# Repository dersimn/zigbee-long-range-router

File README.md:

# CC2530+CC2592 Long Range ZigBee Router
Mod of cod.m's [Zigbee Long Range Router](https://shop.codm.de/automation/zigbee/23/zigbee-cc2530-cc2592-long-range-router/repeater) based on EByte's [E18-MS1PA2-PCB](http://www.ebyte.com/en/product-view-news.aspx?id=988) sporting an CC2530 combined with an CC2592 PA/LNA for range extension.

The corresponding eagle library for the EByte modules, including 3D models, can be found here: https://github.com/codm/eagle-libraries

You can buy a ready built router, including external antenna, 3D printed case and power supply at our webshop: [CC2530-CC2592 Long Range ZigBee Router](https://shop.codm.de/automation/zigbee/23/zigbee-cc2530-cc2592-long-range-router/repeater)

# Firmware
Thanks to https://ptvo.info and his [configurable ZigBee Firmware](https://ptvo.info/zigbee-switch-configurable-firmware-v2-210/), we've built our own version of the firmware - based on Z-Stack 1.2 - to make use of the onboard LED.

See zigbee2mqtt's FAQ for more info on how to use ZigBee routers and expand your current ZigBee mesh: https://www.zigbee2mqtt.io/information/FAQ.html#i-read-that-zigbee2mqtt-has-a-limit-of-20-devices-is-this-true

## Upgrading
You can flash the module with a another/new firmware using an CC-Debugger from TI, which is also used for the common CC2531-USB-Sticks. The pin header on the top has the same layout.

# License
[CC-BY-SA-NC 3.0](https://creativecommons.org/licenses/by-nc-sa/3.0/de/)

Credits:
- cod.m GmbH, Patrik Mayer, 2020
- [Simon Christmann](https://github.com/dersimn), 2020

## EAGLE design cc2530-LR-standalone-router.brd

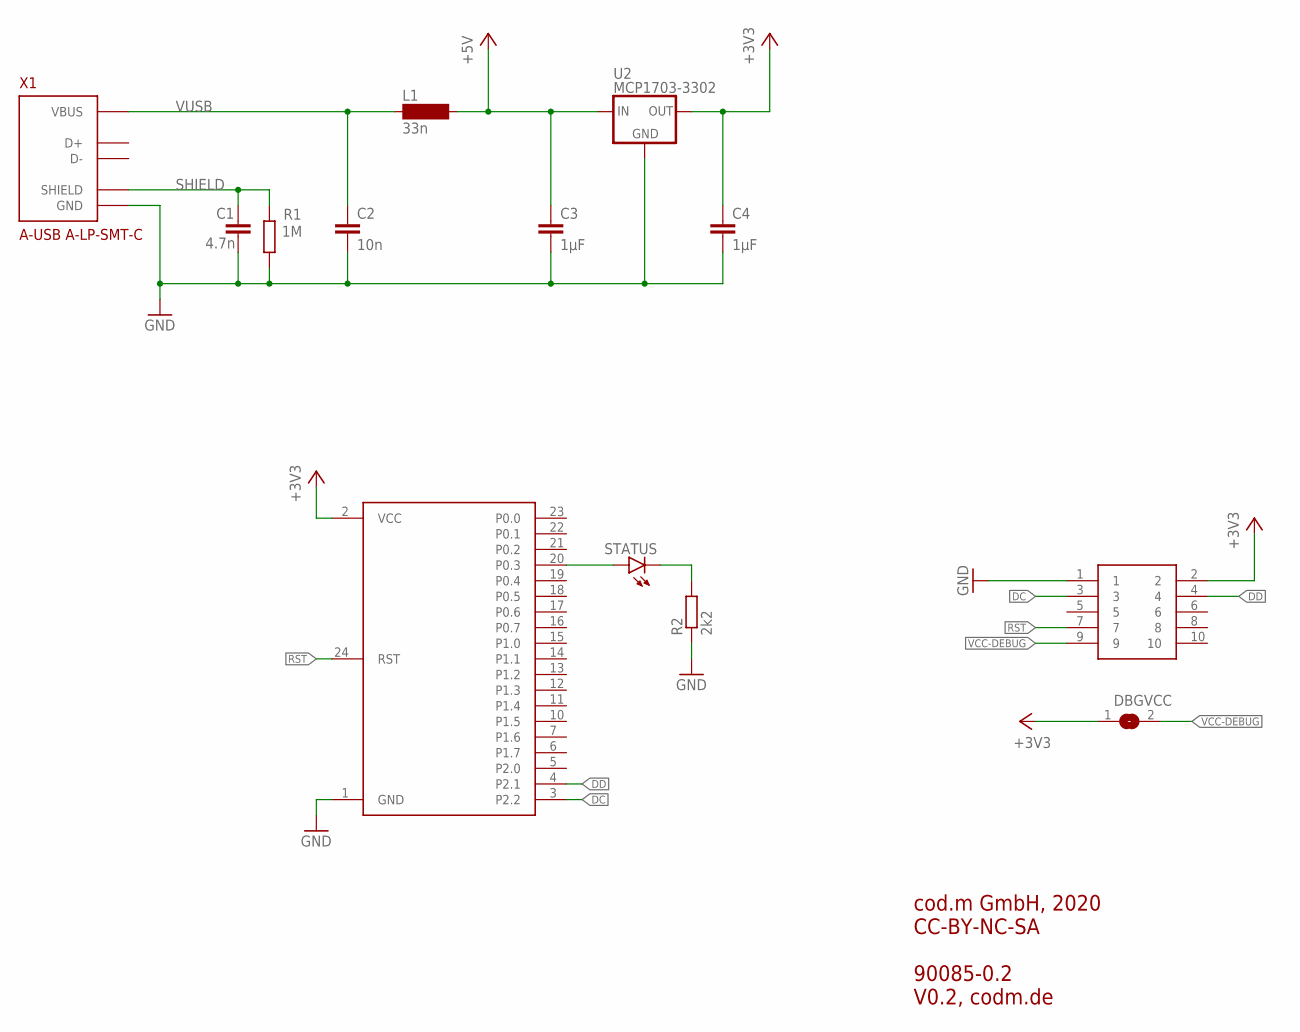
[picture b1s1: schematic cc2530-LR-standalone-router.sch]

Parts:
C1: 4.7n; C1206
C2: 10n; C1206
C3, C4: 1µF; C1206
DBGVCC: SJ
DEBUG: 20021121-00010C4LF; 2002112100010C4LF
L1: 33n; SM-1206
R1: 1M; R1206
R2: 2k2; R1206
STATUS: LEDCHIPLED_1206; CHIPLED_1206
U2: MCP1703-3302; SOT-22-3
U$5: E18-MS1PA2-PCB
X1: A-USB A-LP-SMT-C; A-USB_A-LP-SMT-C

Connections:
+3V3: C4.1, DBGVCC.1, DEBUG.2, U2.3 (OUT), U$5.2 (VCC)
+5V: C3.1, L1.2, U2.1 (IN)
DC: DEBUG.3, U$5.3 (P2.2)
DD: DEBUG.4, U$5.4 (P2.1)
GND: C1.2, C2.2, C3.2, C4.2, DEBUG.1, R1.2, R2.1, U2.2 (GND), U2.4 (GND), U$5.1 (GND), X1.4 (GND)
unnamed: R2.2, STATUS.C
unnamed: STATUS.A, U$5.20 (P0.3)
RST: DEBUG.7, U$5.24 (RST)
SHIELD: C1.1, R1.1, X1.S1 (SHIELD), X1.S2 (SHIELD)
VCC-DEBUG: DBGVCC.2, DEBUG.9
VUSB: C2.1, L1.1, X1.1 (VBUS)

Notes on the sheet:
cod.m GmbH, 2020 CC-BY-NC-SA 90085-0.2 V0.2, codm.de

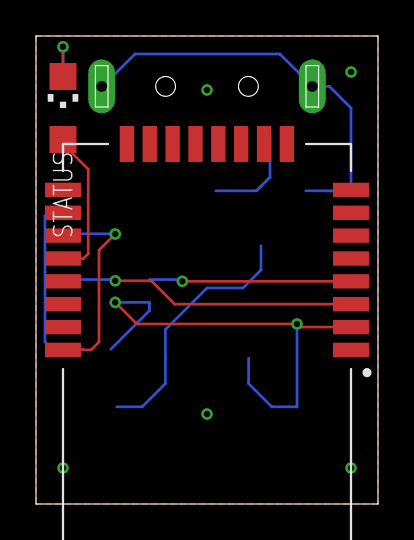
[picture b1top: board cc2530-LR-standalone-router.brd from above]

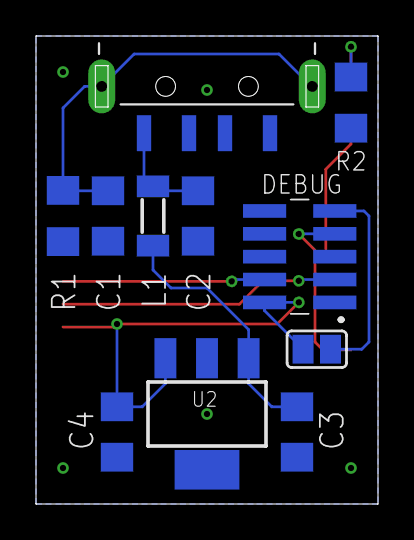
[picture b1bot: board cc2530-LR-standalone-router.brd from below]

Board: 2 copper layers, 19.0 x 26.0 mm, 13 parts (11 on the bottom side), 11 nets.

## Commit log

2020-10-15 Modified Version (USB Stick)
